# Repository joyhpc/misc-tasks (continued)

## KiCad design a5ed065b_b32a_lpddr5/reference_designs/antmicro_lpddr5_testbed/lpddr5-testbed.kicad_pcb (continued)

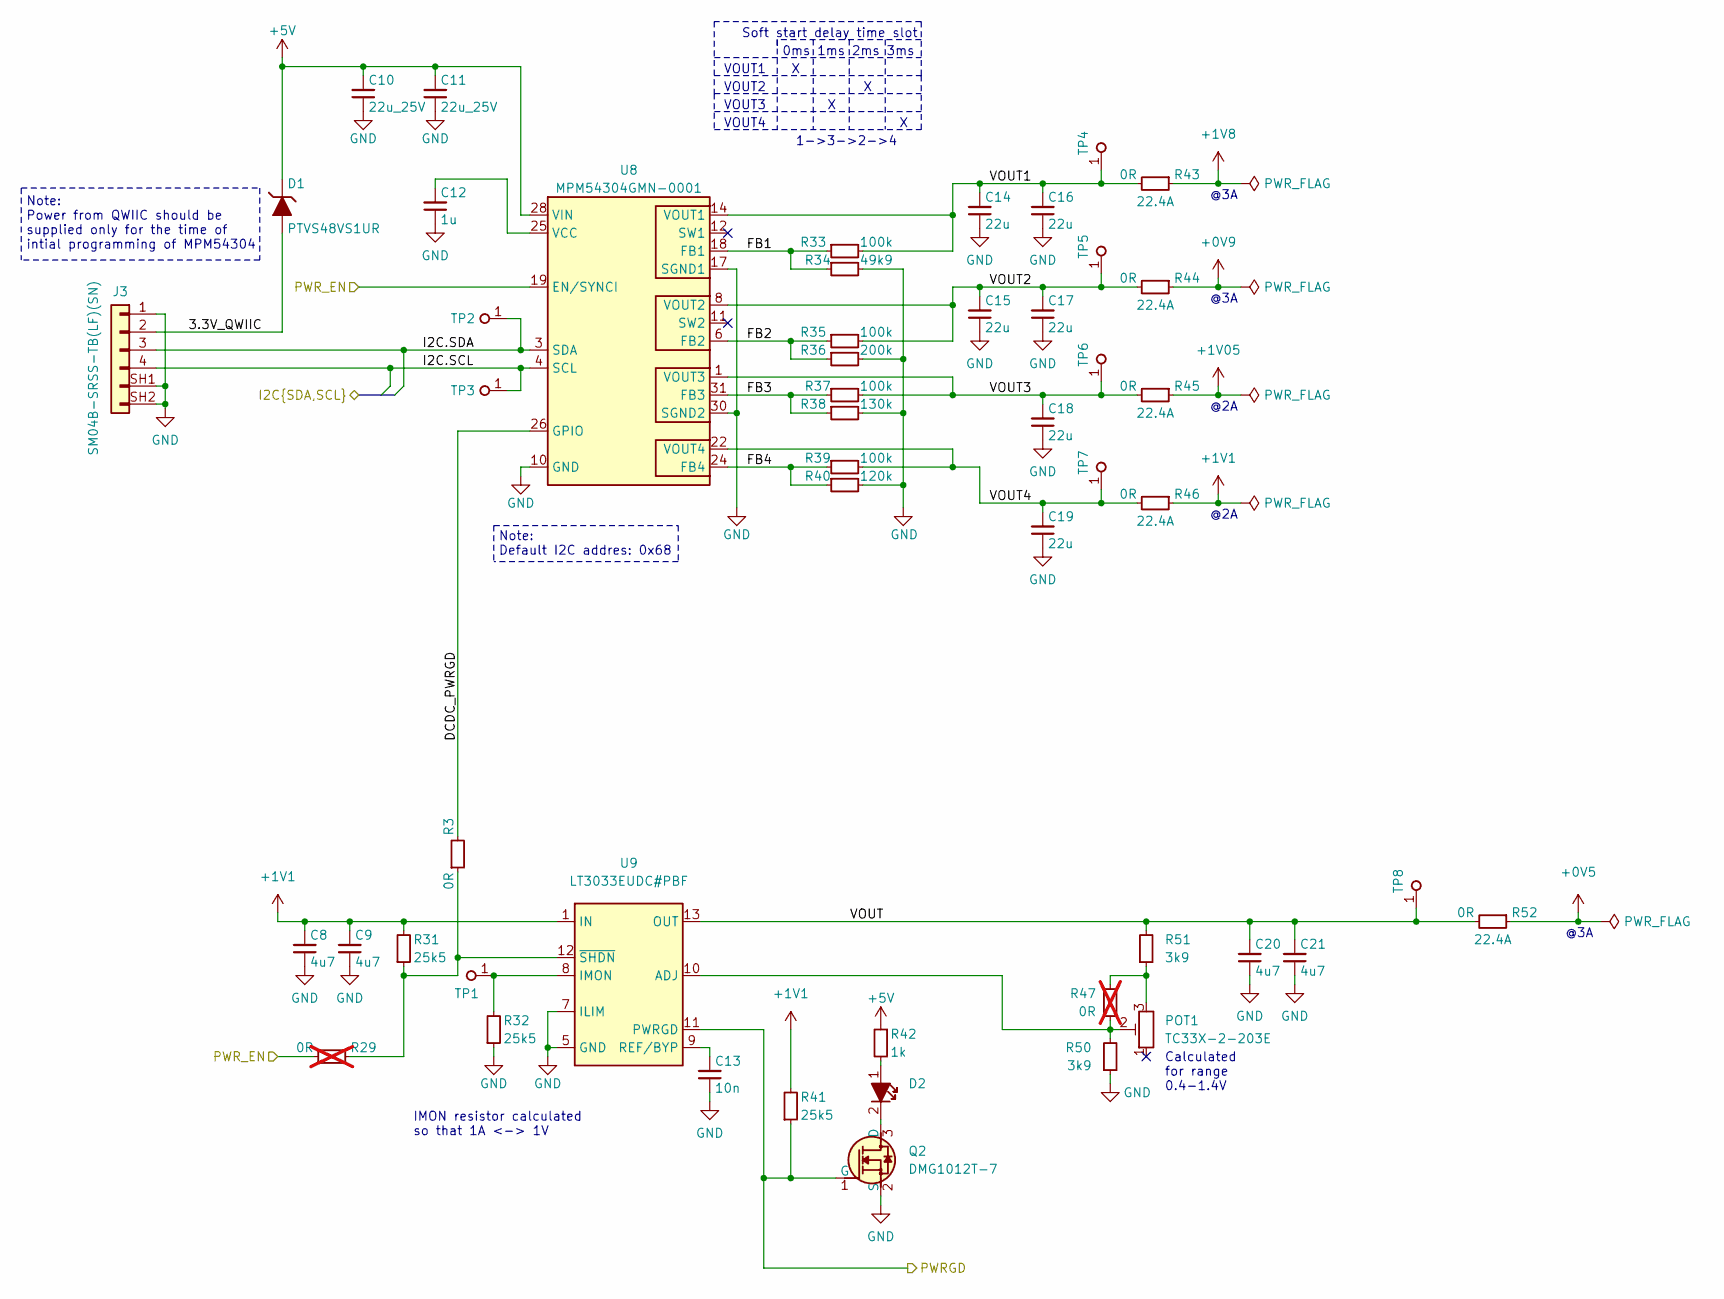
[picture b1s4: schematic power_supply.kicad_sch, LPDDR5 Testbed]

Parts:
C8, C9, C20, C21: C_4u7_0402; C_0402_1005Metric; MPN GRM155R61A475MEAAD
C10, C11: C_22u_25V_0805; C_0805_2012Metric; MPN CL21A226MAYNNNE
C12: C_1u_0402; C_0402_1005Metric; MPN C1005X6S1A105K050BC
C13: C_10n_0402; C_0402_1005Metric; Voltage 50V; MPN GRM155R71H103KA88D
C14, C15, C16, C17, C18, C19: C_22u_0603; C_0603_1608Metric; MPN GRM188R60J226MEA0D
D1: PTVS48VS1UR; D_SOD-123F; MPN PTVS48VS1UR,115
D2: LED_G_0603_KP-1608CGCK; LED_0603_1608Metric_G; MPN KP-1608CGCK
J3: JST_SH_1x4_SM04B-SRSS-TB-LF-SN; Conn_JST_SH_1x4_SM04B-SRSS-TB-LF-SN; MPN SM04B-SRSS-TB(LF)(SN)
POT1: TC33X-2-203E; Trimpot_3.8mmx3.6mm_TC33X-2-103E; MPN TC33X-2-203E
Q2: DMG1012T-7; SOT-523; MPN DMG1012T-7
R3: R_0R_0402; R_0402_1005Metric; MPN ERJ2GE0R00X
R29, R47: R_0R_0402; R_0402_1005Metric; MPN ERJ2GE0R00X; not fitted
R31, R32, R41: R_25k5_0402; R_0402_1005Metric; Tolerance 1%; MPN CR0402-FX-2552GLF
R33, R35, R37, R39: R_100k_0402; R_0402_1005Metric; Tolerance 1%; MPN CR0402-FX-1003GLF
R34: R_49k9_0402; R_0402_1005Metric; Tolerance 1%; MPN CR0402-FX-4992GLF
R36: R_200k_0402; R_0402_1005Metric; Tolerance 1%; MPN CR0402-FX-2003GLF
R38: R_130k_0402; R_0402_1005Metric; Tolerance 1%; MPN CR0402-FX-1303GLF
R40: R_120k_0402; R_0402_1005Metric; Tolerance 1%; MPN CR0402-FX-1203GLF
R42: R_1k_0402; R_0402_1005Metric; Tolerance 1%; MPN CR0402-FX-1001GLF
R43, R44, R45, R46, R52: R_0R_22.4A_0603; R_0603_1608Metric; Tolerance template_tolerance; MPN PMR03EZPJ000
R50, R51: R_3k9_0402; R_0402_1005Metric; Tolerance 1%; MPN CR0402-FX-3901GLF
TP1, TP4, TP5, TP6, TP7, TP8: TP_0.75mm_SMD; TP_SMD_0.75mm
TP2, TP3: TP_1mm_SMD; TP_SMD_1mm
U8: MPM54304GMN-0001; LGA-33_7x7mm_P0.65mm; MPN MPM54304GMN-0001
U9: LT3033EUDC_QFN; QFN-20-4EP_3x4x0.75mm_P0.5mm_Layout4x6_LT3033; MPN LT3033EUDC#PBF

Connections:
+0V5: R52.1; also elsewhere on the board
+0V9: R44.1; also elsewhere on the board
+1V1: C8.2, C9.2, R31.2, R41.2, R46.1, U9.1 (IN), U9.2 (IN), U9.15 (IN), U9.16 (IN), U9.21 (IN), U9.22 (IN)
+1V05: R45.1; also elsewhere on the board
+1V8: R43.1; also elsewhere on the board
+5V: C10.2, C11.2, D1.K (C), R42.1, U8.28 (VIN), U8.29 (VIN); also elsewhere on the board
/Power supply/3.3V_QWIIC: D1.A, J3.2
/Power supply/DCDC_PWRGD: R3.2, U8.26 (GPIO)
/Power supply/FB1: R33.1, R34.1, U8.18 (FB1)
/Power supply/FB2: R35.1, R36.1, U8.6 (FB2)
/Power supply/FB3: R37.1, R38.1, U8.31 (FB3)
/Power supply/FB4: R39.1, R40.1, U8.24 (FB4)
/Power supply/I2C.SCL: J3.4, TP3.1, U8.4 (SCL); also elsewhere on the board
/Power supply/I2C.SDA: J3.3, TP2.1, U8.3 (SDA); also elsewhere on the board
/Power supply/PWRGD: Q2.1 (G), R41.1, U9.11 (PWRGD); also elsewhere on the board
/Power supply/PWR_EN: R29.1, U8.19 (EN/SYNCI); also elsewhere on the board
/Power supply/VOUT: C20.2, C21.2, R51.2, R52.2, TP8.1, U9.3 (OUT), U9.4 (OUT), U9.13 (OUT), U9.14 (OUT), U9.17 (OUT), U9.18 (OUT), U9.19 (OUT), U9.20 (OUT), U9.23 (OUT), U9.24 (OUT)
/Power supply/VOUT1: C14.2, C16.2, R33.2, R43.2, TP4.1, U8.14 (VOUT1), U8.15 (VOUT1)
/Power supply/VOUT2: C15.2, C17.2, R35.2, R44.2, TP5.1, U8.8 (VOUT2), U8.9 (VOUT2)
/Power supply/VOUT3: C18.2, R37.2, R45.2, TP6.1, U8.1 (VOUT3), U8.32 (VOUT3)
/Power supply/VOUT4: C19.2, R39.2, R46.2, TP7.1, U8.22 (VOUT4), U8.23 (VOUT4)
GND: C8.1, C9.1, C10.1, C11.1, C12.1, C13.1, C14.1, C15.1, C16.1, C17.1, C18.1, C19.1, C20.1, C21.1, J3.1, J3.SH1, J3.SH2, Q2.2 (S), R32.1, R34.2, R36.2, R38.2, R40.2, R50.1, U8.2 (GND), U8.5 (GND), U8.7 (GND), U8.10 (GND), U8.13 (GND), U8.16 (GND), U8.17 (SGND1), U8.20 (GND), U8.21 (GND), U8.27 (GND), U8.30 (SGND2), U8.33 (GND), U9.5 (GND), U9.6 (GND), U9.7 (ILIM); also elsewhere on the board
unnamed: C12.2, U8.25 (VCC)
unnamed: C13.2, U9.9 (REF/BYP)
unnamed: D2.1, R42.2
unnamed: D2.2, Q2.3 (D)
unnamed: POT1.2, R47.1, R50.2, U9.10 (ADJ)
unnamed: POT1.3, R47.2, R51.1
unnamed: R3.1, R29.2, R31.1, U9.12 (~SHDN)
unnamed: R32.2, TP1.1, U9.8 (IMON)

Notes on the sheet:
@2A
Soft start delay time slot
VOUT4
VOUT1
@3A
Note: Default I2C addres: 0x68
Note: Power from QWIIC should be supplied only for the time of intial programming of MPM54304
Calculated for range 0.4-1.4V
1->3->2->4
VOUT3
VOUT2
0ms 1ms 2ms 3ms
IMON resistor calculated so that 1A <-> 1V

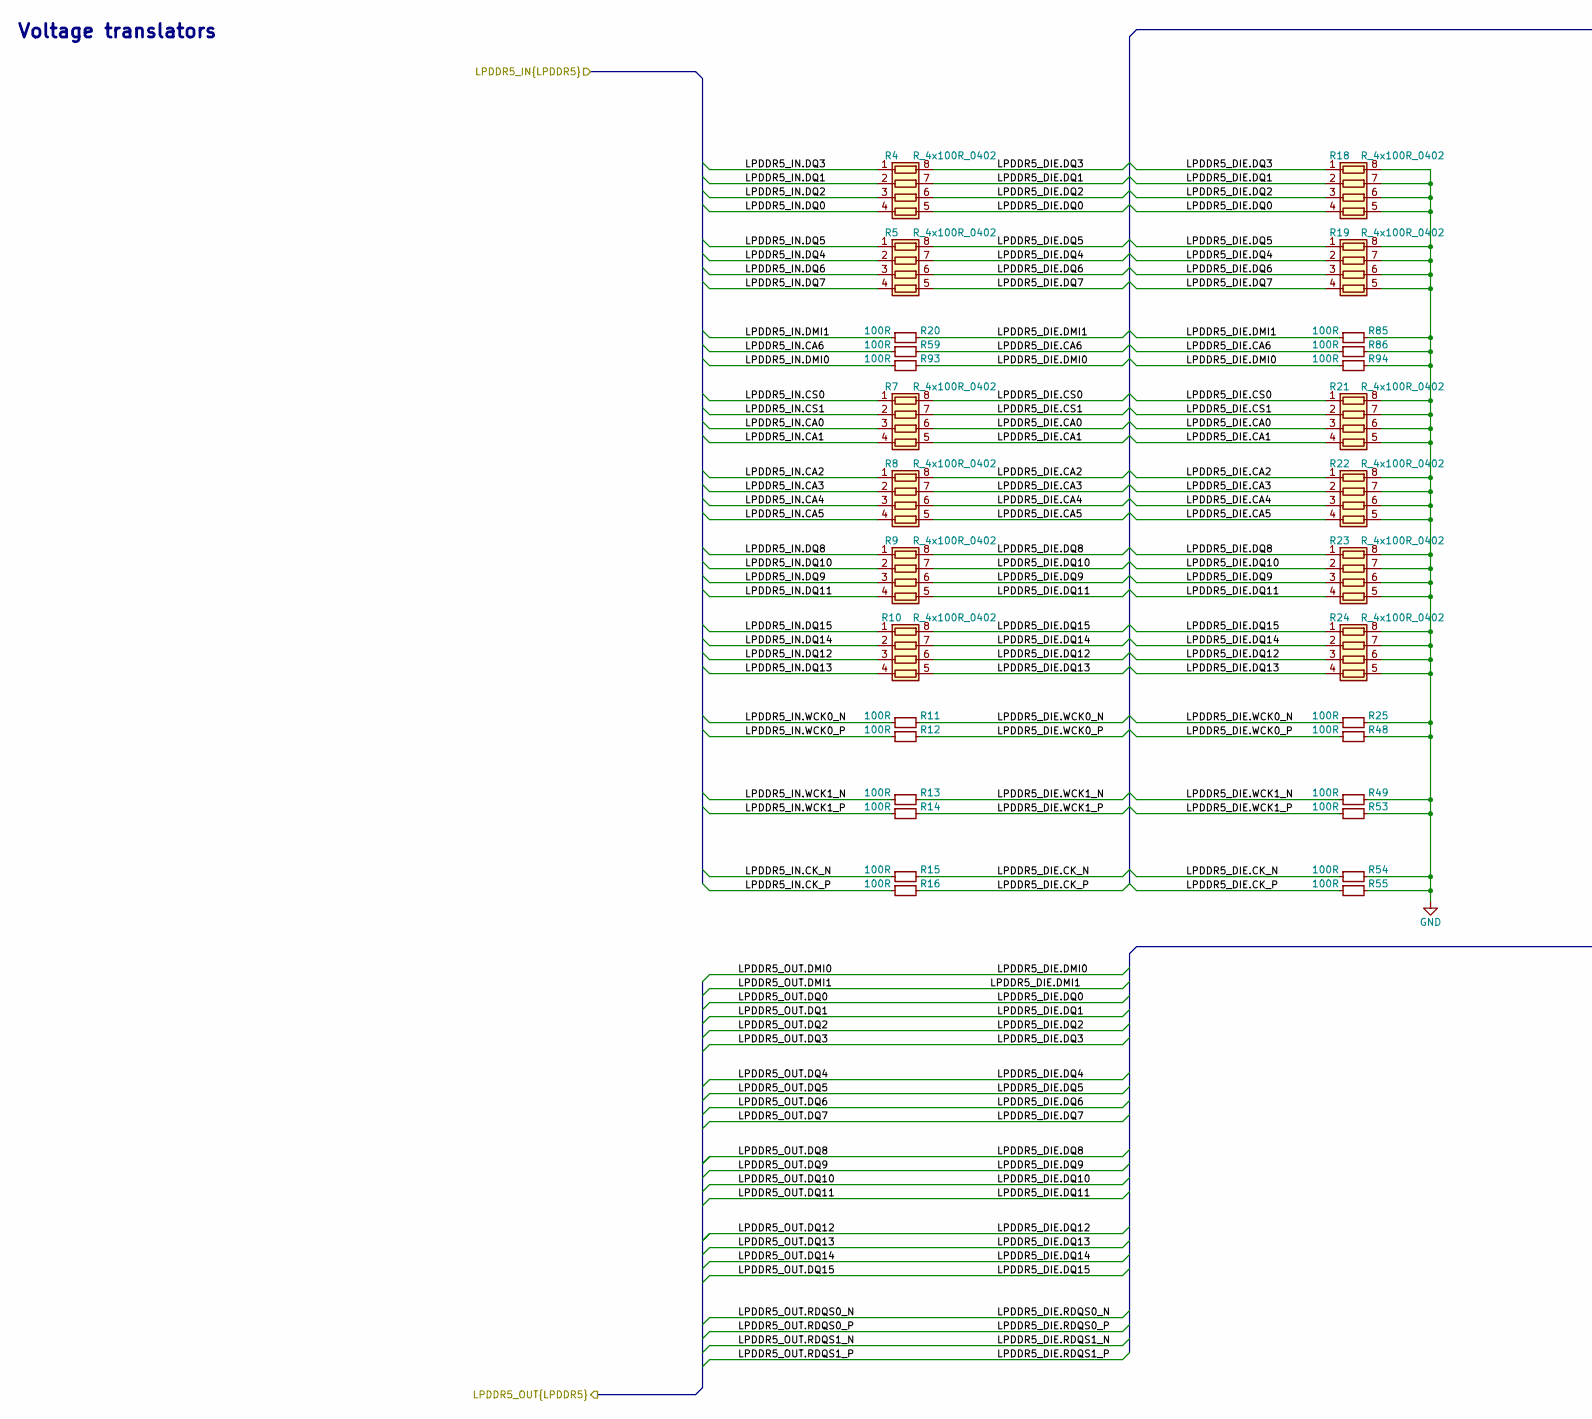
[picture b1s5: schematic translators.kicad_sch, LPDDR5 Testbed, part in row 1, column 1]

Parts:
R4, R5, R7, R8, R9, R10, R18, R19, R21, R22, R23, R24: R_4x100R_0402_array; R_Array_4x0402_Panasonic_EXB28V; MPN EXB-28V101JX
R11, R12, R13, R14, R15, R16, R20, R25, R48, R49, R53, R54, R55, R59, R85, R86, R93, R94: R_100R_0402; R_0402_1005Metric; Tolerance 1%; MPN CR0402-FX-1000GLF

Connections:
/LPDDR5/LPDDR5_A.CA0: R7.6 (R3.2), R21.3 (R3.1); also elsewhere on the board
/LPDDR5/LPDDR5_A.CA1: R7.5 (R4.2), R21.4 (R4.1); also elsewhere on the board
/LPDDR5/LPDDR5_A.CA2: R8.8 (R1.2), R22.1 (R1.1); also elsewhere on the board
/LPDDR5/LPDDR5_A.CA3: R8.7 (R2.2), R22.2 (R2.1); also elsewhere on the board
/LPDDR5/LPDDR5_A.CA4: R8.6 (R3.2), R22.3 (R3.1); also elsewhere on the board
/LPDDR5/LPDDR5_A.CA5: R8.5 (R4.2), R22.4 (R4.1); also elsewhere on the board
/LPDDR5/LPDDR5_A.CA6: R59.2, R86.1; also elsewhere on the board
/LPDDR5/LPDDR5_A.CK_N: R15.2, R54.1; also elsewhere on the board
/LPDDR5/LPDDR5_A.CK_P: R16.2, R55.1; also elsewhere on the board
/LPDDR5/LPDDR5_A.CS0: R7.8 (R1.2), R21.1 (R1.1); also elsewhere on the board
/LPDDR5/LPDDR5_A.CS1: R7.7 (R2.2), R21.2 (R2.1); also elsewhere on the board
/LPDDR5/LPDDR5_A.DMI0: R93.2, R94.1; also elsewhere on the board
/LPDDR5/LPDDR5_A.DMI1: R20.2, R85.1; also elsewhere on the board
/LPDDR5/LPDDR5_A.DQ0: R4.5 (R4.2), R18.4 (R4.1); also elsewhere on the board
/LPDDR5/LPDDR5_A.DQ1: R4.7 (R2.2), R18.2 (R2.1); also elsewhere on the board
/LPDDR5/LPDDR5_A.DQ2: R4.6 (R3.2), R18.3 (R3.1); also elsewhere on the board
/LPDDR5/LPDDR5_A.DQ3: R4.8 (R1.2), R18.1 (R1.1); also elsewhere on the board
/LPDDR5/LPDDR5_A.DQ4: R5.7 (R2.2), R19.2 (R2.1); also elsewhere on the board
/LPDDR5/LPDDR5_A.DQ5: R5.8 (R1.2), R19.1 (R1.1); also elsewhere on the board
/LPDDR5/LPDDR5_A.DQ6: R5.6 (R3.2), R19.3 (R3.1); also elsewhere on the board
/LPDDR5/LPDDR5_A.DQ7: R5.5 (R4.2), R19.4 (R4.1); also elsewhere on the board
/LPDDR5/LPDDR5_A.DQ8: R9.8 (R1.2), R23.1 (R1.1); also elsewhere on the board
/LPDDR5/LPDDR5_A.DQ9: R9.6 (R3.2), R23.3 (R3.1); also elsewhere on the board
/LPDDR5/LPDDR5_A.DQ10: R9.7 (R2.2), R23.2 (R2.1); also elsewhere on the board
/LPDDR5/LPDDR5_A.DQ11: R9.5 (R4.2), R23.4 (R4.1); also elsewhere on the board
/LPDDR5/LPDDR5_A.DQ12: R10.6 (R3.2), R24.3 (R3.1); also elsewhere on the board
/LPDDR5/LPDDR5_A.DQ13: R10.5 (R4.2), R24.4 (R4.1); also elsewhere on the board
/LPDDR5/LPDDR5_A.DQ14: R10.7 (R2.2), R24.2 (R2.1); also elsewhere on the board
/LPDDR5/LPDDR5_A.DQ15: R10.8 (R1.2), R24.1 (R1.1); also elsewhere on the board
/LPDDR5/LPDDR5_A.WCK0_N: R11.2, R25.1; also elsewhere on the board
/LPDDR5/LPDDR5_A.WCK0_P: R12.2, R48.1; also elsewhere on the board
/LPDDR5/LPDDR5_A.WCK1_N: R13.2, R49.1; also elsewhere on the board
/LPDDR5/LPDDR5_A.WCK1_P: R14.2, R53.1; also elsewhere on the board
/SODIMM/LPDDR5_IN_A.CA0: R7.3 (R3.1); also elsewhere on the board
/SODIMM/LPDDR5_IN_A.CA1: R7.4 (R4.1); also elsewhere on the board
/SODIMM/LPDDR5_IN_A.CA2: R8.1 (R1.1); also elsewhere on the board
/SODIMM/LPDDR5_IN_A.CA3: R8.2 (R2.1); also elsewhere on the board
/SODIMM/LPDDR5_IN_A.CA4: R8.3 (R3.1); also elsewhere on the board
/SODIMM/LPDDR5_IN_A.CA5: R8.4 (R4.1); also elsewhere on the board
/SODIMM/LPDDR5_IN_A.CA6: R59.1; also elsewhere on the board
/SODIMM/LPDDR5_IN_A.CK_N: R15.1; also elsewhere on the board
/SODIMM/LPDDR5_IN_A.CK_P: R16.1; also elsewhere on the board
/SODIMM/LPDDR5_IN_A.CS0: R7.1 (R1.1); also elsewhere on the board
/SODIMM/LPDDR5_IN_A.CS1: R7.2 (R2.1); also elsewhere on the board
/SODIMM/LPDDR5_IN_A.DMI0: R93.1; also elsewhere on the board
/SODIMM/LPDDR5_IN_A.DMI1: R20.1; also elsewhere on the board
/SODIMM/LPDDR5_IN_A.DQ0: R4.4 (R4.1); also elsewhere on the board
/SODIMM/LPDDR5_IN_A.DQ1: R4.2 (R2.1); also elsewhere on the board
/SODIMM/LPDDR5_IN_A.DQ2: R4.3 (R3.1); also elsewhere on the board
/SODIMM/LPDDR5_IN_A.DQ3: R4.1 (R1.1); also elsewhere on the board
/SODIMM/LPDDR5_IN_A.DQ4: R5.2 (R2.1); also elsewhere on the board
/SODIMM/LPDDR5_IN_A.DQ5: R5.1 (R1.1); also elsewhere on the board
/SODIMM/LPDDR5_IN_A.DQ6: R5.3 (R3.1); also elsewhere on the board
/SODIMM/LPDDR5_IN_A.DQ7: R5.4 (R4.1); also elsewhere on the board
/SODIMM/LPDDR5_IN_A.DQ8: R9.1 (R1.1); also elsewhere on the board
/SODIMM/LPDDR5_IN_A.DQ9: R9.3 (R3.1); also elsewhere on the board
/SODIMM/LPDDR5_IN_A.DQ10: R9.2 (R2.1); also elsewhere on the board
/SODIMM/LPDDR5_IN_A.DQ11: R9.4 (R4.1); also elsewhere on the board
/SODIMM/LPDDR5_IN_A.DQ12: R10.3 (R3.1); also elsewhere on the board
/SODIMM/LPDDR5_IN_A.DQ13: R10.4 (R4.1); also elsewhere on the board
/SODIMM/LPDDR5_IN_A.DQ14: R10.2 (R2.1); also elsewhere on the board
/SODIMM/LPDDR5_IN_A.DQ15: R10.1 (R1.1); also elsewhere on the board
/SODIMM/LPDDR5_IN_A.WCK0_N: R11.1; also elsewhere on the board
/SODIMM/LPDDR5_IN_A.WCK0_P: R12.1; also elsewhere on the board
/SODIMM/LPDDR5_IN_A.WCK1_N: R13.1; also elsewhere on the board
/SODIMM/LPDDR5_IN_A.WCK1_P: R14.1; also elsewhere on the board
GND: R18.5 (R4.2), R18.6 (R3.2), R18.7 (R2.2), R18.8 (R1.2), R19.5 (R4.2), R19.6 (R3.2), R19.7 (R2.2), R19.8 (R1.2), R21.5 (R4.2), R21.6 (R3.2), R21.7 (R2.2), R21.8 (R1.2), R22.5 (R4.2), R22.6 (R3.2), R22.7 (R2.2), R22.8 (R1.2), R23.5 (R4.2), R23.6 (R3.2), R23.7 (R2.2), R23.8 (R1.2), R24.5 (R4.2), R24.6 (R3.2), R24.7 (R2.2), R24.8 (R1.2), R25.2, R48.2, R49.2, R53.2, R54.2, R55.2, R85.2, R86.2, R94.2; also elsewhere on the board

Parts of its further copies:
R57, R58, R60, R61, R62, R63, R72, R73, R75, R76, R77, R78: R_4x100R_0402_array; R_Array_4x0402_Panasonic_EXB28V; MPN EXB-28V101JX
R64, R65, R66, R67, R68, R70, R79, R80, R81, R82, R83, R84, R88, R89, R91, R92, R95, R96: R_100R_0402; R_0402_1005Metric; Tolerance 1%; MPN CR0402-FX-1000GLF

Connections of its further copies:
/LPDDR5/LPDDR5_B.CA0: R60.6 (R3.2), R75.3 (R3.1); also elsewhere on the board
/LPDDR5/LPDDR5_B.CA1: R60.5 (R4.2), R75.4 (R4.1); also elsewhere on the board
/LPDDR5/LPDDR5_B.CA2: R61.8 (R1.2), R76.1 (R1.1); also elsewhere on the board
/LPDDR5/LPDDR5_B.CA3: R61.7 (R2.2), R76.2 (R2.1); also elsewhere on the board
/LPDDR5/LPDDR5_B.CA4: R61.6 (R3.2), R76.3 (R3.1); also elsewhere on the board
/LPDDR5/LPDDR5_B.CA5: R61.5 (R4.2), R76.4 (R4.1); also elsewhere on the board
/LPDDR5/LPDDR5_B.CA6: R89.2, R92.1; also elsewhere on the board
/LPDDR5/LPDDR5_B.CK_N: R68.2, R83.1; also elsewhere on the board
/LPDDR5/LPDDR5_B.CK_P: R70.2, R84.1; also elsewhere on the board
/LPDDR5/LPDDR5_B.CS0: R60.8 (R1.2), R75.1 (R1.1); also elsewhere on the board
/LPDDR5/LPDDR5_B.CS1: R60.7 (R2.2), R75.2 (R2.1); also elsewhere on the board
/LPDDR5/LPDDR5_B.DMI0: R95.2, R96.1; also elsewhere on the board
/LPDDR5/LPDDR5_B.DMI1: R88.2, R91.1; also elsewhere on the board
/LPDDR5/LPDDR5_B.DQ0: R57.5 (R4.2), R72.4 (R4.1); also elsewhere on the board
/LPDDR5/LPDDR5_B.DQ1: R57.7 (R2.2), R72.2 (R2.1); also elsewhere on the board
/LPDDR5/LPDDR5_B.DQ2: R57.6 (R3.2), R72.3 (R3.1); also elsewhere on the board
/LPDDR5/LPDDR5_B.DQ3: R57.8 (R1.2), R72.1 (R1.1); also elsewhere on the board
/LPDDR5/LPDDR5_B.DQ4: R58.7 (R2.2), R73.2 (R2.1); also elsewhere on the board
/LPDDR5/LPDDR5_B.DQ5: R58.8 (R1.2), R73.1 (R1.1); also elsewhere on the board
/LPDDR5/LPDDR5_B.DQ6: R58.6 (R3.2), R73.3 (R3.1); also elsewhere on the board
/LPDDR5/LPDDR5_B.DQ7: R58.5 (R4.2), R73.4 (R4.1); also elsewhere on the board
/LPDDR5/LPDDR5_B.DQ8: R62.8 (R1.2), R77.1 (R1.1); also elsewhere on the board
/LPDDR5/LPDDR5_B.DQ9: R62.6 (R3.2), R77.3 (R3.1); also elsewhere on the board
/LPDDR5/LPDDR5_B.DQ10: R62.7 (R2.2), R77.2 (R2.1); also elsewhere on the board
/LPDDR5/LPDDR5_B.DQ11: R62.5 (R4.2), R77.4 (R4.1); also elsewhere on the board
/LPDDR5/LPDDR5_B.DQ12: R63.6 (R3.2), R78.3 (R3.1); also elsewhere on the board
/LPDDR5/LPDDR5_B.DQ13: R63.5 (R4.2), R78.4 (R4.1); also elsewhere on the board
/LPDDR5/LPDDR5_B.DQ14: R63.7 (R2.2), R78.2 (R2.1); also elsewhere on the board
/LPDDR5/LPDDR5_B.DQ15: R63.8 (R1.2), R78.1 (R1.1); also elsewhere on the board
/LPDDR5/LPDDR5_B.WCK0_N: R64.2, R79.1; also elsewhere on the board
/LPDDR5/LPDDR5_B.WCK0_P: R65.2, R80.1; also elsewhere on the board
/LPDDR5/LPDDR5_B.WCK1_N: R66.2, R81.1; also elsewhere on the board
/LPDDR5/LPDDR5_B.WCK1_P: R67.2, R82.1; also elsewhere on the board
/SODIMM/LPDDR5_IN_B.CA0: R60.3 (R3.1); also elsewhere on the board
/SODIMM/LPDDR5_IN_B.CA1: R60.4 (R4.1); also elsewhere on the board
/SODIMM/LPDDR5_IN_B.CA2: R61.1 (R1.1); also elsewhere on the board
/SODIMM/LPDDR5_IN_B.CA3: R61.2 (R2.1); also elsewhere on the board
/SODIMM/LPDDR5_IN_B.CA4: R61.3 (R3.1); also elsewhere on the board
/SODIMM/LPDDR5_IN_B.CA5: R61.4 (R4.1); also elsewhere on the board
/SODIMM/LPDDR5_IN_B.CA6: R89.1; also elsewhere on the board
/SODIMM/LPDDR5_IN_B.CK_N: R68.1; also elsewhere on the board
/SODIMM/LPDDR5_IN_B.CK_P: R70.1; also elsewhere on the board
/SODIMM/LPDDR5_IN_B.CS0: R60.1 (R1.1); also elsewhere on the board
/SODIMM/LPDDR5_IN_B.CS1: R60.2 (R2.1); also elsewhere on the board
/SODIMM/LPDDR5_IN_B.DMI0: R95.1; also elsewhere on the board
/SODIMM/LPDDR5_IN_B.DMI1: R88.1; also elsewhere on the board
/SODIMM/LPDDR5_IN_B.DQ0: R57.4 (R4.1); also elsewhere on the board
/SODIMM/LPDDR5_IN_B.DQ1: R57.2 (R2.1); also elsewhere on the board
/SODIMM/LPDDR5_IN_B.DQ2: R57.3 (R3.1); also elsewhere on the board
/SODIMM/LPDDR5_IN_B.DQ3: R57.1 (R1.1); also elsewhere on the board
/SODIMM/LPDDR5_IN_B.DQ4: R58.2 (R2.1); also elsewhere on the board
/SODIMM/LPDDR5_IN_B.DQ5: R58.1 (R1.1); also elsewhere on the board
/SODIMM/LPDDR5_IN_B.DQ6: R58.3 (R3.1); also elsewhere on the board
/SODIMM/LPDDR5_IN_B.DQ7: R58.4 (R4.1); also elsewhere on the board
/SODIMM/LPDDR5_IN_B.DQ8: R62.1 (R1.1); also elsewhere on the board
/SODIMM/LPDDR5_IN_B.DQ9: R62.3 (R3.1); also elsewhere on the board
/SODIMM/LPDDR5_IN_B.DQ10: R62.2 (R2.1); also elsewhere on the board
/SODIMM/LPDDR5_IN_B.DQ11: R62.4 (R4.1); also elsewhere on the board
/SODIMM/LPDDR5_IN_B.DQ12: R63.3 (R3.1); also elsewhere on the board
/SODIMM/LPDDR5_IN_B.DQ13: R63.4 (R4.1); also elsewhere on the board
/SODIMM/LPDDR5_IN_B.DQ14: R63.2 (R2.1); also elsewhere on the board
/SODIMM/LPDDR5_IN_B.DQ15: R63.1 (R1.1); also elsewhere on the board
/SODIMM/LPDDR5_IN_B.WCK0_N: R64.1; also elsewhere on the board
/SODIMM/LPDDR5_IN_B.WCK0_P: R65.1; also elsewhere on the board
/SODIMM/LPDDR5_IN_B.WCK1_N: R66.1; also elsewhere on the board
/SODIMM/LPDDR5_IN_B.WCK1_P: R67.1; also elsewhere on the board
GND: R72.5 (R4.2), R72.6 (R3.2), R72.7 (R2.2), R72.8 (R1.2), R73.5 (R4.2), R73.6 (R3.2), R73.7 (R2.2), R73.8 (R1.2), R75.5 (R4.2), R75.6 (R3.2), R75.7 (R2.2), R75.8 (R1.2), R76.5 (R4.2), R76.6 (R3.2), R76.7 (R2.2), R76.8 (R1.2), R77.5 (R4.2), R77.6 (R3.2), R77.7 (R2.2), R77.8 (R1.2), R78.5 (R4.2), R78.6 (R3.2), R78.7 (R2.2), R78.8 (R1.2), R79.2, R80.2, R81.2, R82.2, R83.2, R84.2, R91.2, R92.2, R96.2; also elsewhere on the board

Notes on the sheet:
Voltage translators

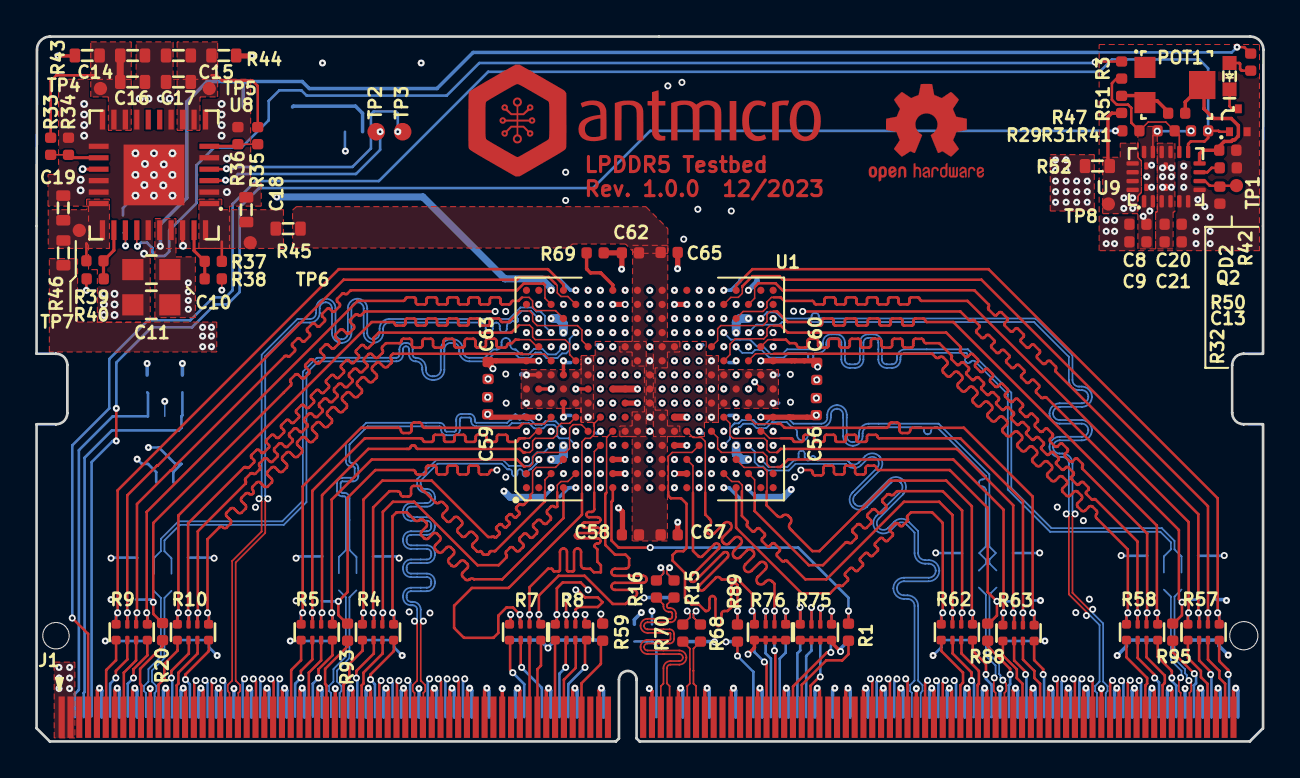
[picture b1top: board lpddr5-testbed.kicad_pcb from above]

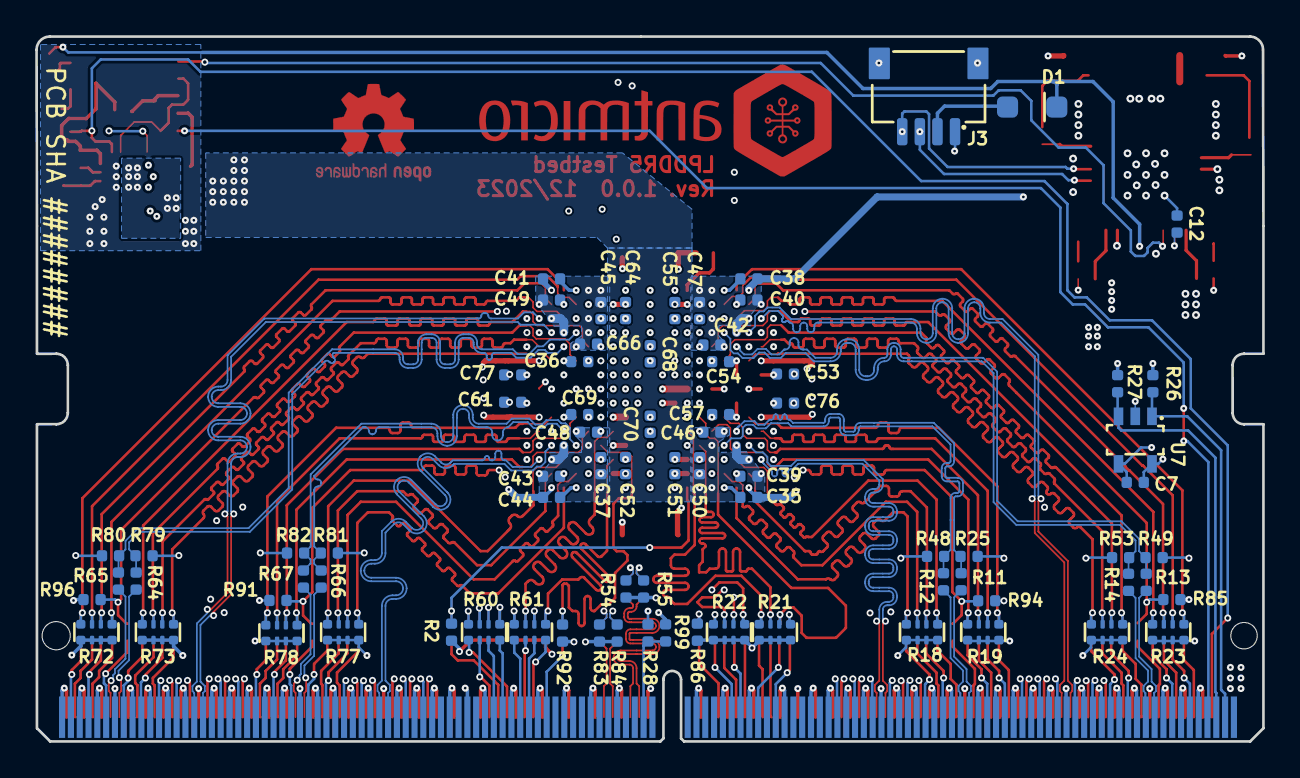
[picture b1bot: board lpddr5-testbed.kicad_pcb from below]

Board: 6 copper layers, 69.6 x 40.0 mm, 160 parts (78 on the bottom side), 176 nets.

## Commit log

2026-05-11 Initial misc tasks archive
2026-05-11 Add LPDDR5 reference materials
2026-05-11 Add OrCAD LPDDR5 ECAD sources
2026-05-12 docs: add DDR memory supplier inquiry template
2026-05-12 docs: add DDR memory supplier inquiry table
2026-05-12 docs: add DDR memory supplier inquiry workbook
2026-05-12 docs: add supplier-facing DDR inquiry workbook
